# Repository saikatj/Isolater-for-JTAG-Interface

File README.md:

# Isolator for JTAG interfae
 This module provides an electrical isolation for commonly availble JTAG debugging interfaces
 The design is created using KiCad 5.1

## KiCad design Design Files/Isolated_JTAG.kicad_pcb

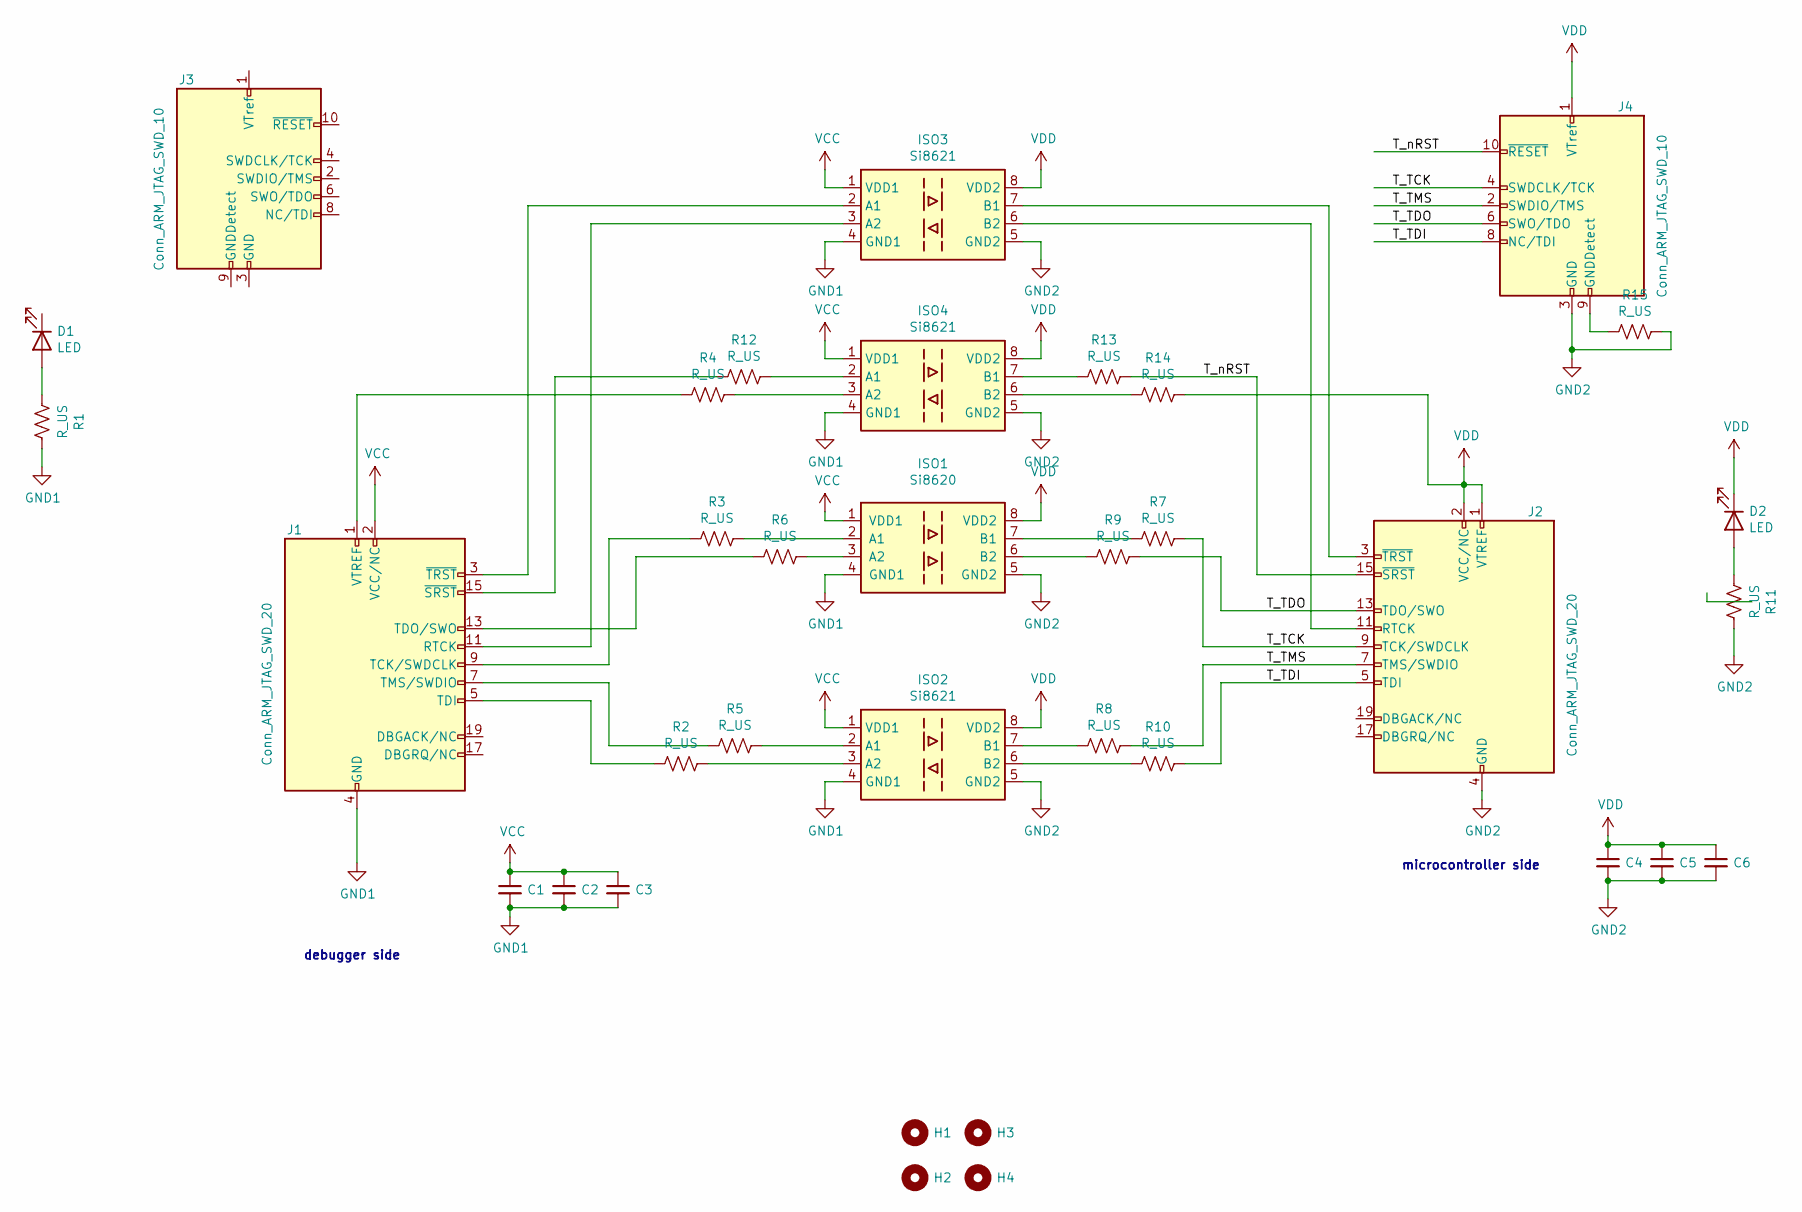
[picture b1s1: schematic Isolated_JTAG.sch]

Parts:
C1, C2, C3, C4, C5, C6: C_Small; C_0805_2012Metric_Pad1.18x1.45mm_HandSolder
D1, D2: LED; LED_0805_2012Metric_Pad1.15x1.40mm_HandSolder
H1, H2, H3, H4: MountingHole; MountingHole_3.2mm_M3
ISO1: Si8620; SOIC-8_3.9x4.9mm_P1.27mm
ISO2, ISO3, ISO4: Si8621; SOIC-8_3.9x4.9mm_P1.27mm
J1, J2: Conn_ARM_JTAG_SWD_20; IDC-Header_2x10_P2.54mm_Vertical
J3, J4: Conn_ARM_JTAG_SWD_10; IDC-Header_2x05_P2.54mm_Vertical
R1, R2, R3, R4, R5, R6, R7, R8, R9, R10, R11, R12, R13, R14, R15: R_US; R_0805_2012Metric_Pad1.20x1.40mm_HandSolder

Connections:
/T_TCK: J2.9 (TCK/SWDCLK), J4.4 (SWDCLK/TCK), R7.1
/T_TDI: J2.5 (TDI), J4.8 (NC/TDI), R10.1
/T_TDO: J2.13 (TDO/SWO), J4.6 (SWO/TDO), R9.1
/T_TMS: J2.7 (TMS/SWDIO), J4.2 (SWDIO/TMS), R8.1
/T_nRST: J2.15 (~SRST~), J4.10 (~RESET~), R13.1
GND1: C1.2, C2.2, C3.2, ISO1.4 (GND1), ISO2.4 (GND1), ISO3.4 (GND1), ISO4.4 (GND1), J1.4 (GND), R1.1
GND2: C4.2, C5.2, C6.2, ISO1.5 (GND2), ISO2.5 (GND2), ISO3.5 (GND2), ISO4.5 (GND2), J2.4 (GND), J4.3 (GND), J4.5 (GND), R11.1, R15.1
unnamed: D1.2 (A), R1.2
unnamed: D2.2 (A), R11.2
unnamed: ISO1.2 (A1), R3.1
unnamed: ISO1.3 (A2), R6.1
unnamed: ISO1.6 (B2), R9.2
unnamed: ISO1.7 (B1), R7.2
unnamed: ISO2.2 (A1), R5.1
unnamed: ISO2.3 (A2), R2.1
unnamed: ISO2.6 (B2), R10.2
unnamed: ISO2.7 (B1), R8.2
unnamed: ISO3.2 (A1), J1.3 (~TRST~)
unnamed: ISO3.3 (A2), J1.11 (RTCK)
unnamed: ISO3.6 (B2), J2.11 (RTCK)
unnamed: ISO3.7 (B1), J2.3 (~TRST~)
unnamed: ISO4.2 (A1), R12.1
unnamed: ISO4.3 (A2), R4.1
unnamed: ISO4.6 (B2), R14.2
unnamed: ISO4.7 (B1), R13.2
unnamed: J1.1 (VTREF), R4.2
unnamed: J1.5 (TDI), R2.2
unnamed: J1.7 (TMS/SWDIO), R5.2
unnamed: J1.9 (TCK/SWDCLK), R3.2
unnamed: J1.13 (TDO/SWO), R6.2
unnamed: J1.15 (~SRST~), R12.2
unnamed: J3.3 (GND), J3.5 (GND)
unnamed: J4.9 (GNDDetect), R15.2
VCC: C1.1, C2.1, C3.1, ISO1.1 (VDD1), ISO2.1 (VDD1), ISO3.1 (VDD1), ISO4.1 (VDD1), J1.2 (VCC/NC)
VDD: C4.1, C5.1, C6.1, D2.1 (K), ISO1.8 (VDD2), ISO2.8 (VDD2), ISO3.8 (VDD2), ISO4.8 (VDD2), J2.1 (VTREF), J2.2 (VCC/NC), J4.1 (VTref), R14.1

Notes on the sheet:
debugger side
microcontroller side

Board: 2 copper layers, 35 parts (0 on the bottom side), 35 nets, no tracks yet.

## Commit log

2021-09-19 added photos
